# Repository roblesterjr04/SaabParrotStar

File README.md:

# SaabParrotStar
Arduino project designed to interface between Saab's onstar buttons and a parrot CK3000 evo handsfree unit.

## Operation
### Standby
|Button     |Action    |Function                 |
|:---------:|:--------:|:-----------------------:|
|*OnStar*   |Press Once|Activate Siri/Answer Call|
|--         |Hold      |Redial                   |
|Dot        |Press Once|Enter Menu               |
|--         |Hold      |Enable/Disable Aux 1     |
|Red Cross  |Press Once|--                       |
|--         |Hold      |Enable/Disable Aux 2     |
|--         |Long Hold |Reset Parrot             |

### In Call
|Button     |Action    |Function                 |
|:---------:|:--------:|:-----------------------:|
|*OnStar*   |Press Once|Call Waiting/Private Mode|
|--         |Hold      |Redial                   |
|Dot        |Press Once|Volume Up                |
|--         |Hold      |Volume Down              |
|Red Cross  |Press Once|Hang Up                  |
|--         |Hold      |Hang Up                  |

### Menu Operation
|Button     |Action    |Function                 |
|:---------:|:--------:|:-----------------------:|
|*OnStar*   |Press Once|Select                   |
|--         |Hold      |--                       |
|Dot        |Press Once|Down                     |
|--         |Hold      |--                       |
|Red Cross  |Press Once|Up                       |
|--         |Hold      |Exit                     |

## Board Version History
### Version *1.0 (A328.brd)*
This board uses the ATMega328P chip and an external 16MHz crystal. Chip should be bootloaded and programmed before installed on the board. The traces for the 12V switching relays are rated for 1.42A, though the G5V1 relays are only rated at 1A. All traces can handle up to 440mA. The lettering on the connectors are wire color for the 4 pin cable, and by purpose on the 5 pin. The pinout for the 5 pin is so: *P = Power/5v (out), E = Earth/Gnd, A = Analog signal, G = Green Led, R = Red Led*. The pinout for the 4 pin molex is so: *Y = Power/12v (in), B = Earth/Gnd, R = TX, Bl = RX*. The ATMega328P has only one serial port, so the code must be modified to use Serial0, not Serial1 as it is now for development/prototype. The chip needs to be mounted in a socket, as 2 of the resistors are placed under the ship in the recesses of the socket.

<a href="https://oshpark.com/shared_projects/tsGGRMay"></img></a>

## Future Ideas...
Will like to build CK3100 compatability to allow for text display to be piped in to CAN bus and display on Saab's SID display. Would also like to conceive a method to integrate steering wheel controls. Should not be too challenging since they are also an analog circuit.

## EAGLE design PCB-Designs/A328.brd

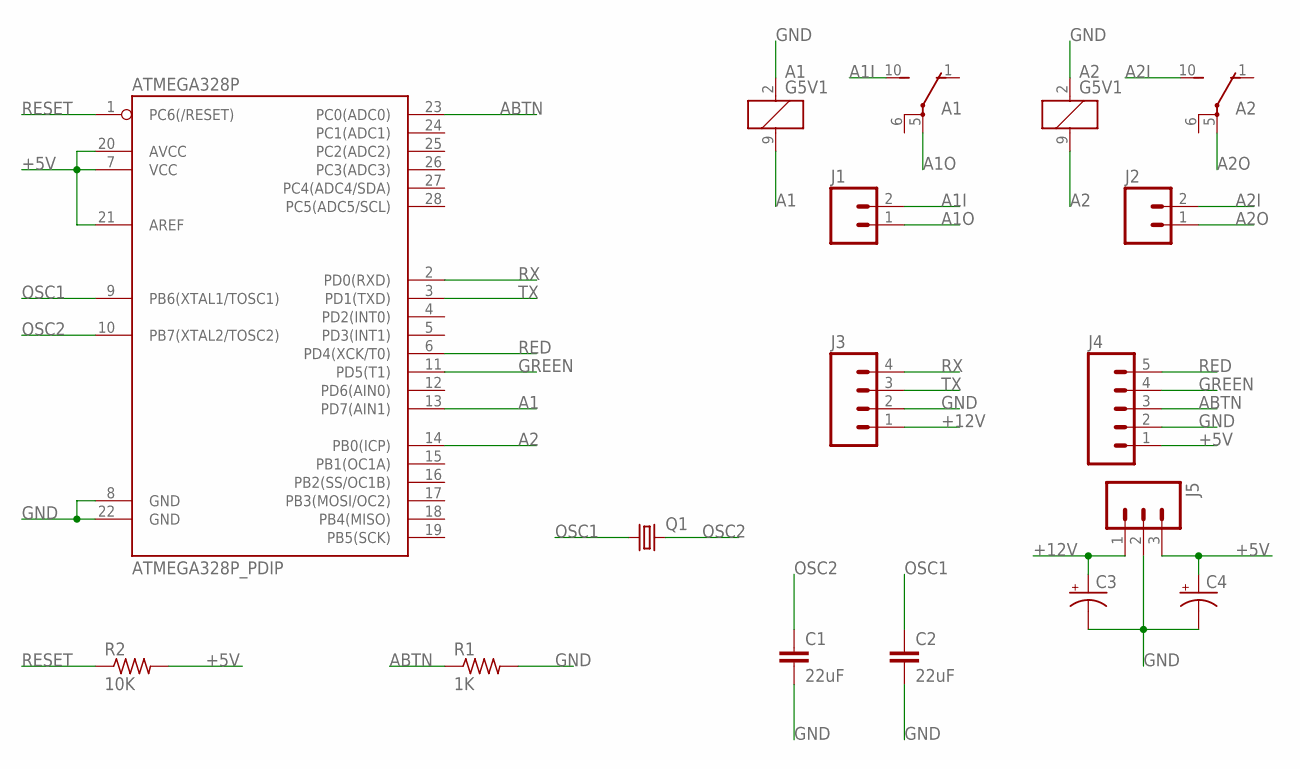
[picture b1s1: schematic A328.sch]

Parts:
A1, A2: G5V1
ATMEGA328P: ATMEGA328P_PDIP; DIL28-3
C1, C2: 22uF; CAP-PTH-SMALL-KIT
C3, C4: 10UF-25V-20%(PTH); CPOL-RADIAL-10UF-25V
J1, J2: M02PTH3; 1X02_LONGPADS
J3: M04NO_SILK_ALL_ROUND; 1X04_NO_SILK_ALL_ROUND
J4: M05NO_SILK; 1X05_NO_SILK
J5: M03LONGPADS; 1X03_LONGPADS
Q1: CRYSTALHC49S; HC49/S
R1: 1K; 0204/7
R2: 10K; 0204/7

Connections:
+5V: ATMEGA328P.7 (VCC), ATMEGA328P.20 (AVCC), ATMEGA328P.21 (AREF), C4.1 (+), J4.1, J5.3, R2.2
+12V: C3.1 (+), J3.1, J5.1
A1: A1.9 (2), ATMEGA328P.13 (PD7(AIN1))
A1I: A1.10 (S), J1.2
A1O: A1.5, J1.1
A2: A2.9 (2), ATMEGA328P.14 (PB0(ICP))
A2I: A2.10 (S), J2.2
A2O: A2.5, J2.1
ABTN: ATMEGA328P.23 (PC0(ADC0)), J4.3, R1.1
GND: A1.2 (1), A2.2 (1), ATMEGA328P.8 (GND), ATMEGA328P.22 (GND), C1.2, C2.2, C3.2 (-), C4.2 (-), J3.2, J4.2, J5.2, R1.2
GREEN: ATMEGA328P.11 (PD5(T1)), J4.4
OSC1: ATMEGA328P.9 (PB6(XTAL1/TOSC1)), C2.1, Q1.1
OSC2: ATMEGA328P.10 (PB7(XTAL2/TOSC2)), C1.1, Q1.2
RED: ATMEGA328P.6 (PD4(XCK/T0)), J4.5
RESET: ATMEGA328P.1 (PC6(/RESET)), R2.1
RX: ATMEGA328P.2 (PD0(RXD)), J3.4
TX: ATMEGA328P.3 (PD1(TXD)), J3.3

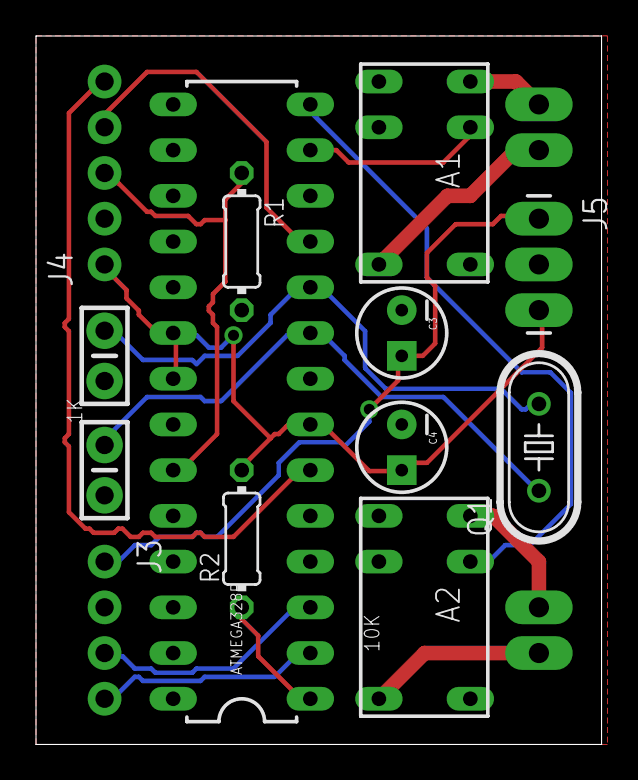
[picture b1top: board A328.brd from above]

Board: 2 copper layers, 31.4 x 39.4 mm, 15 parts (0 on the bottom side), 17 nets.

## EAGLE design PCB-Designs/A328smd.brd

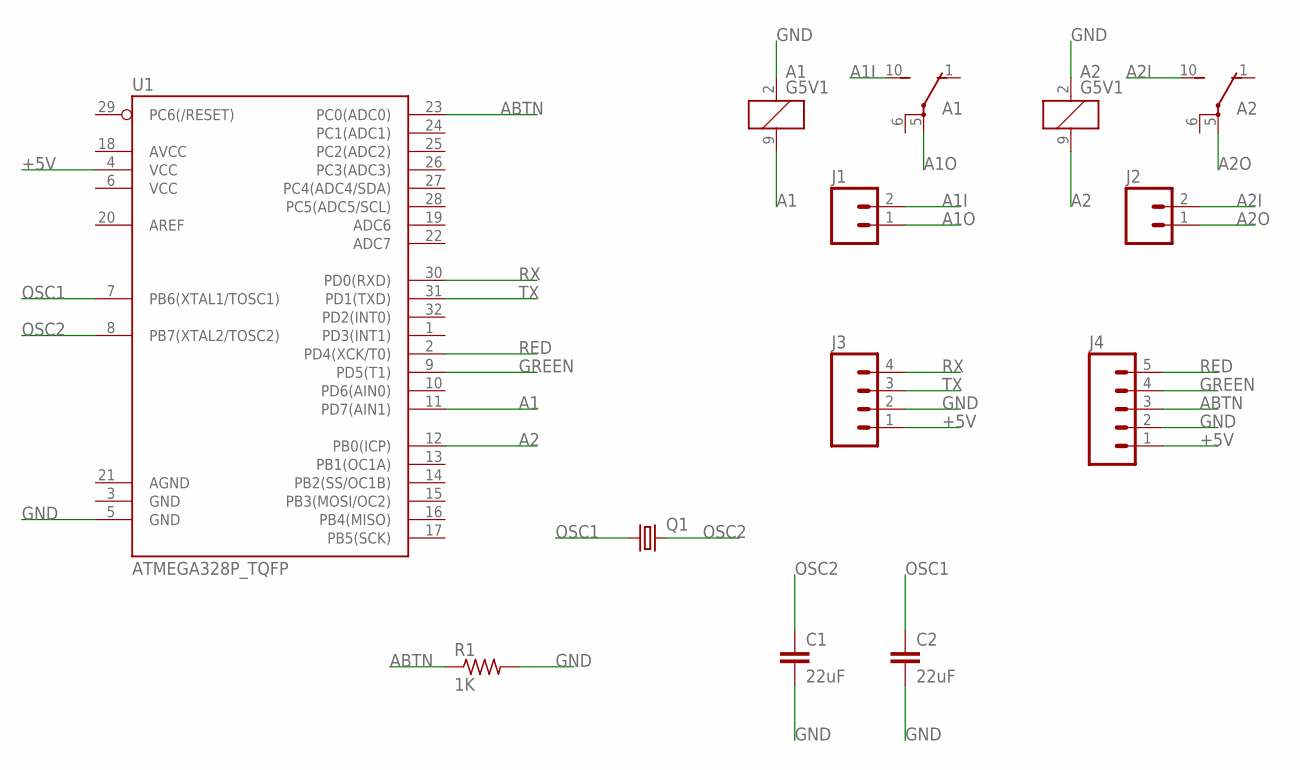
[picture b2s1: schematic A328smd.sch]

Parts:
A1, A2: G5V1
C1, C2: 22uF; 1210
J1, J2: M02PTH3; 1X02_LONGPADS
J3: M04NO_SILK_ALL_ROUND; 1X04_NO_SILK_ALL_ROUND
J4: M05NO_SILK; 1X05_NO_SILK
Q1: CRYSTALSM49; SM49
R1: 1K; M1206
U1: ATMEGA328P_TQFP; TQFP32-08

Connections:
+5V: J3.1, J4.1, U1.4 (VCC)
A1: A1.9 (2), U1.11 (PD7(AIN1))
A1I: A1.10 (S), J1.2
A1O: A1.5, J1.1
A2: A2.9 (2), U1.12 (PB0(ICP))
A2I: A2.10 (S), J2.2
A2O: A2.5, J2.1
ABTN: J4.3, R1.1, U1.23 (PC0(ADC0))
GND: A1.2 (1), A2.2 (1), C1.2, C2.2, J3.2, J4.2, R1.2, U1.5 (GND)
GREEN: J4.4, U1.9 (PD5(T1))
OSC1: C2.1, Q1.1, U1.7 (PB6(XTAL1/TOSC1))
OSC2: C1.1, Q1.2, U1.8 (PB7(XTAL2/TOSC2))
RED: J4.5, U1.2 (PD4(XCK/T0))
RX: J3.4, U1.30 (PD0(RXD))
TX: J3.3, U1.31 (PD1(TXD))

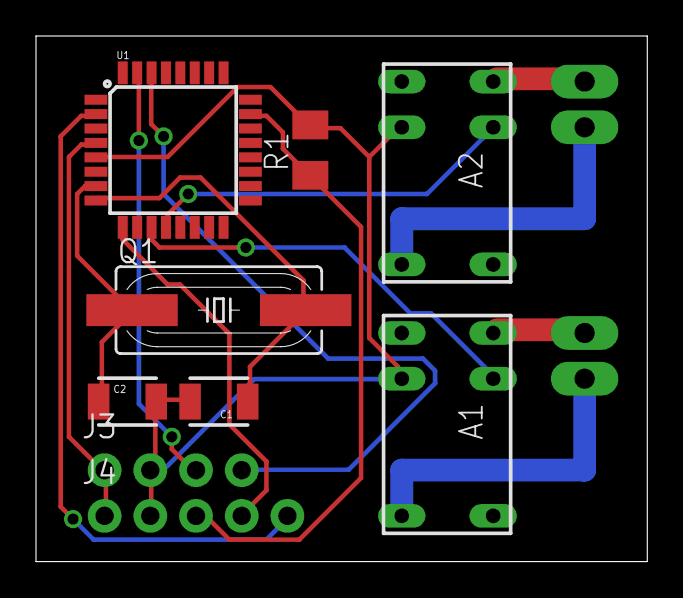
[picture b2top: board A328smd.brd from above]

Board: 2 copper layers, 34.0 x 29.2 mm, 11 parts (0 on the bottom side), 15 nets.

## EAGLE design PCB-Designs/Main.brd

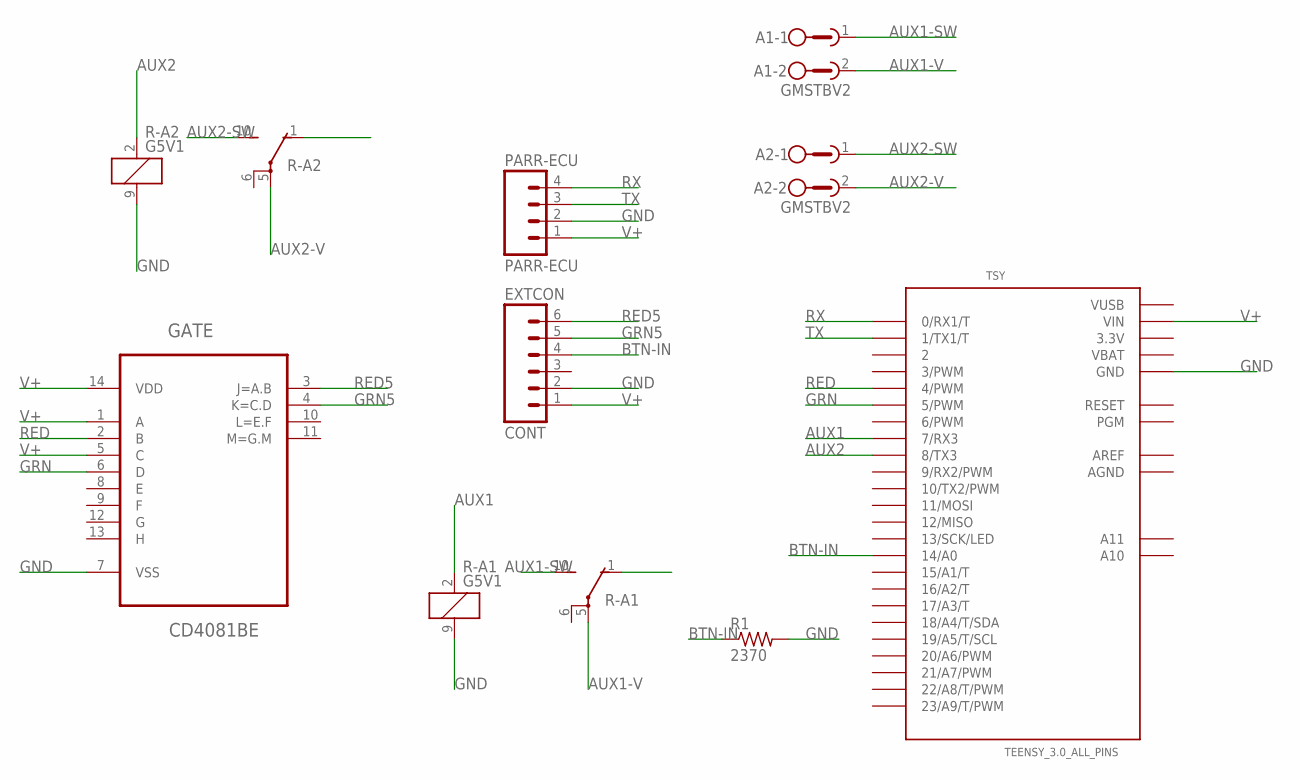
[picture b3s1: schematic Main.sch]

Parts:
A1, A2: GMSTBV2
EXTCON: CONT; 1X06_NO_SILK
GATE: CD4081BE; DIP254P762X508-14
PARR-ECU: PARR-ECU; 1X04_NO_SILK_ALL_ROUND
R1: 2370; 0207/10
R-A1, R-A2: G5V1
TSY: TEENSY_3.0_ALL_PINS; TEENSY_3.0-3.2&LC_ALL_PINS

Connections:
3.3V: TSY.3.3V, TSY.3.3V1 (3.3V)
AGND: TSY.AGND
AREF: TSY.AREF
AUX1: R-A1.2 (1), TSY.7 (7/RX3)
AUX1-SW: A1.1, R-A1.10 (S)
AUX1-V: A1.2, R-A1.5
AUX2: R-A2.2 (1), TSY.8 (8/TX3)
AUX2-SW: A2.1, R-A2.10 (S)
AUX2-V: A2.2, R-A2.5
BTN-IN: EXTCON.4, R1.1, TSY.14/A0
GND: EXTCON.2, GATE.7 (VSS), PARR-ECU.2, R1.2, R-A1.9 (2), R-A2.9 (2), TSY.GND, TSY.GND1 (GND)
GRN: GATE.6 (D), TSY.5 (5/PWM)
GRN5: EXTCON.5, GATE.4 (K=C.D)
RED: GATE.2 (B), TSY.4 (4/PWM)
RED5: EXTCON.6, GATE.3 (J=A.B)
RX: PARR-ECU.4, TSY.0 (0/RX1/T)
TX: PARR-ECU.3, TSY.1 (1/TX1/T)
V+: EXTCON.1, GATE.1 (A), GATE.5 (C), GATE.14 (VDD), PARR-ECU.1, TSY.VIN
VBAT: TSY.VBAT
VUSB: TSY.VUSB

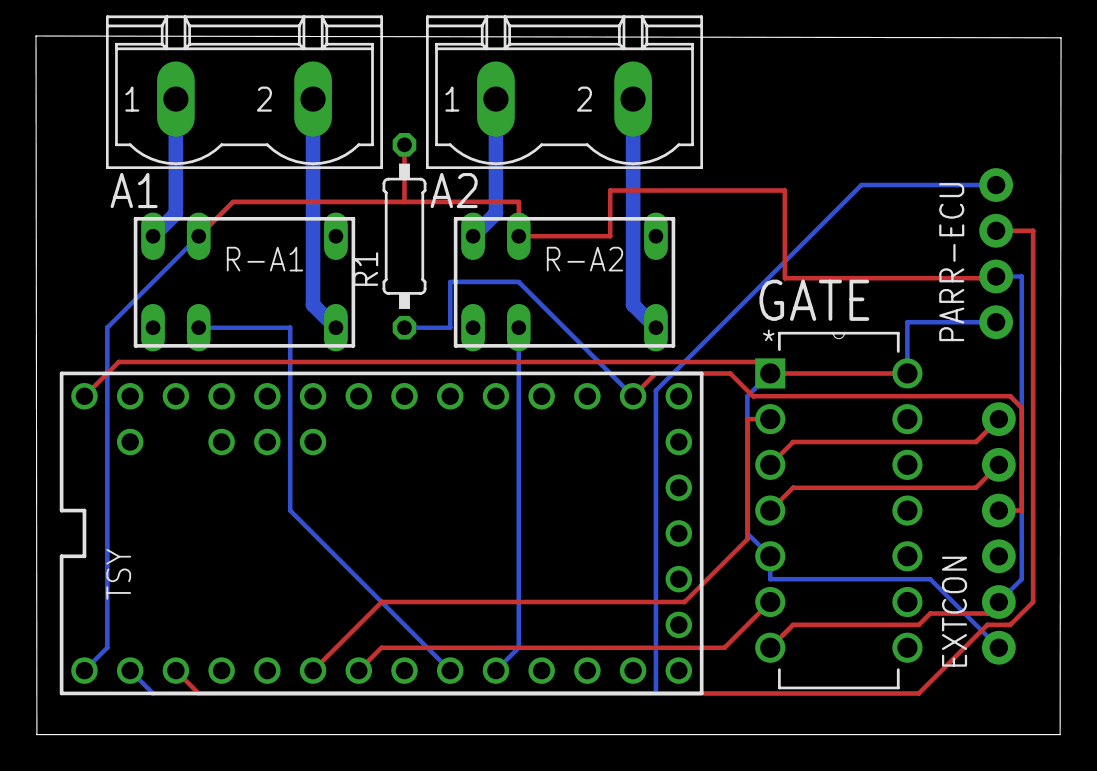
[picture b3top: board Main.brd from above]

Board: 2 copper layers, 56.9 x 38.8 mm, 9 parts (0 on the bottom side), 16 nets.

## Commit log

2016-12-02 Added protocol code to main file.
2016-12-07 Rename ParrotStar.cpp to ParrotStar.ino
2016-12-07 Changed filename
2016-12-07 Analog button signal final
    Read values against a 1k resistor and input to the code. Also removed
    the multi-press functions since multi-press doesn’t work on this
    circuit.
2016-12-07 Code changes and fixes
2016-12-07 Added software reset code
    Added test code to do a hard reset to the parrot module and clear its settings. Needed software reset for the controller so that a handshake could be re-established.
2016-12-07 Removing serial references
    Will eventually remove all Serial.println because final design with atmega328 chip will only have a single Serial port, needed for comms with parrot.
2016-12-08 Code cleanup and values adjusted. Code is good for prototype board.
2016-12-08 Moved serial definition.
2016-12-12 Add PCB designs.
2016-12-12 Added information for beta1 board.
2016-12-12 Updating board files
2016-12-13 Adjusted analog ranges for Teensy3.2
    there must be some noise on the circuit or the resistor i used before
    wasn’t quite 1K.
2016-12-16 Working on final board compatible code.
2016-12-20 PCB Updates to the A328 board.
2016-12-20 Smaller board, redundant power according to arduino schematic.
2016-12-20 Building in multi-chip compatability
    The Teensy does not have a “Serial 0”, it only has Serial 1,2,3 and “0”
    is a software emulation. The Atmega328p has only Serial0 as hardware.
    Building automatic detection of this in the code on compilation so that
    It doesn’t need to be changed per chip.
2016-12-22 Code updates and button diagnostic functions.
2016-12-23 Disconnected the red pin
    Only using a 4 conductor cable to the buttons so there will be no red
    light. The board will support it, but I’ve removed the alternating
    red/green light code so the menu won’t be confusing.
2017-01-06 Updated code to work with Atmega328 only
    Values needed to be tweaked and devices specific code needed to be
    removed. it wasn’t allowing the program to run and therefor didn’t work
    with the Parrot.
2017-05-18 Bug fixes that may fix the problem with answering calls.
2017-05-18 Updated version number and chip model.
2017-05-18 Changed button function slightly
    Remove volume down while in call. Make single press of dot to volume up, make single press of red x to hangup during call.
2017-06-14 Code prettifying
    Organizing code for understandability. Fixing bugs found in logic review.
2017-07-11 Verifying new program was uploaded
2017-07-11 Added board link
2017-08-03 Add ring status, light when big button pressed.
2018-04-17 Call the analog button reader during the serial response.

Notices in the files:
parts and their libraries:
SparkFun-Connectors: Licensing: Creative Commons ShareAlike 4.0 International - https://creativecommons.org/licenses/by-sa/4.0
